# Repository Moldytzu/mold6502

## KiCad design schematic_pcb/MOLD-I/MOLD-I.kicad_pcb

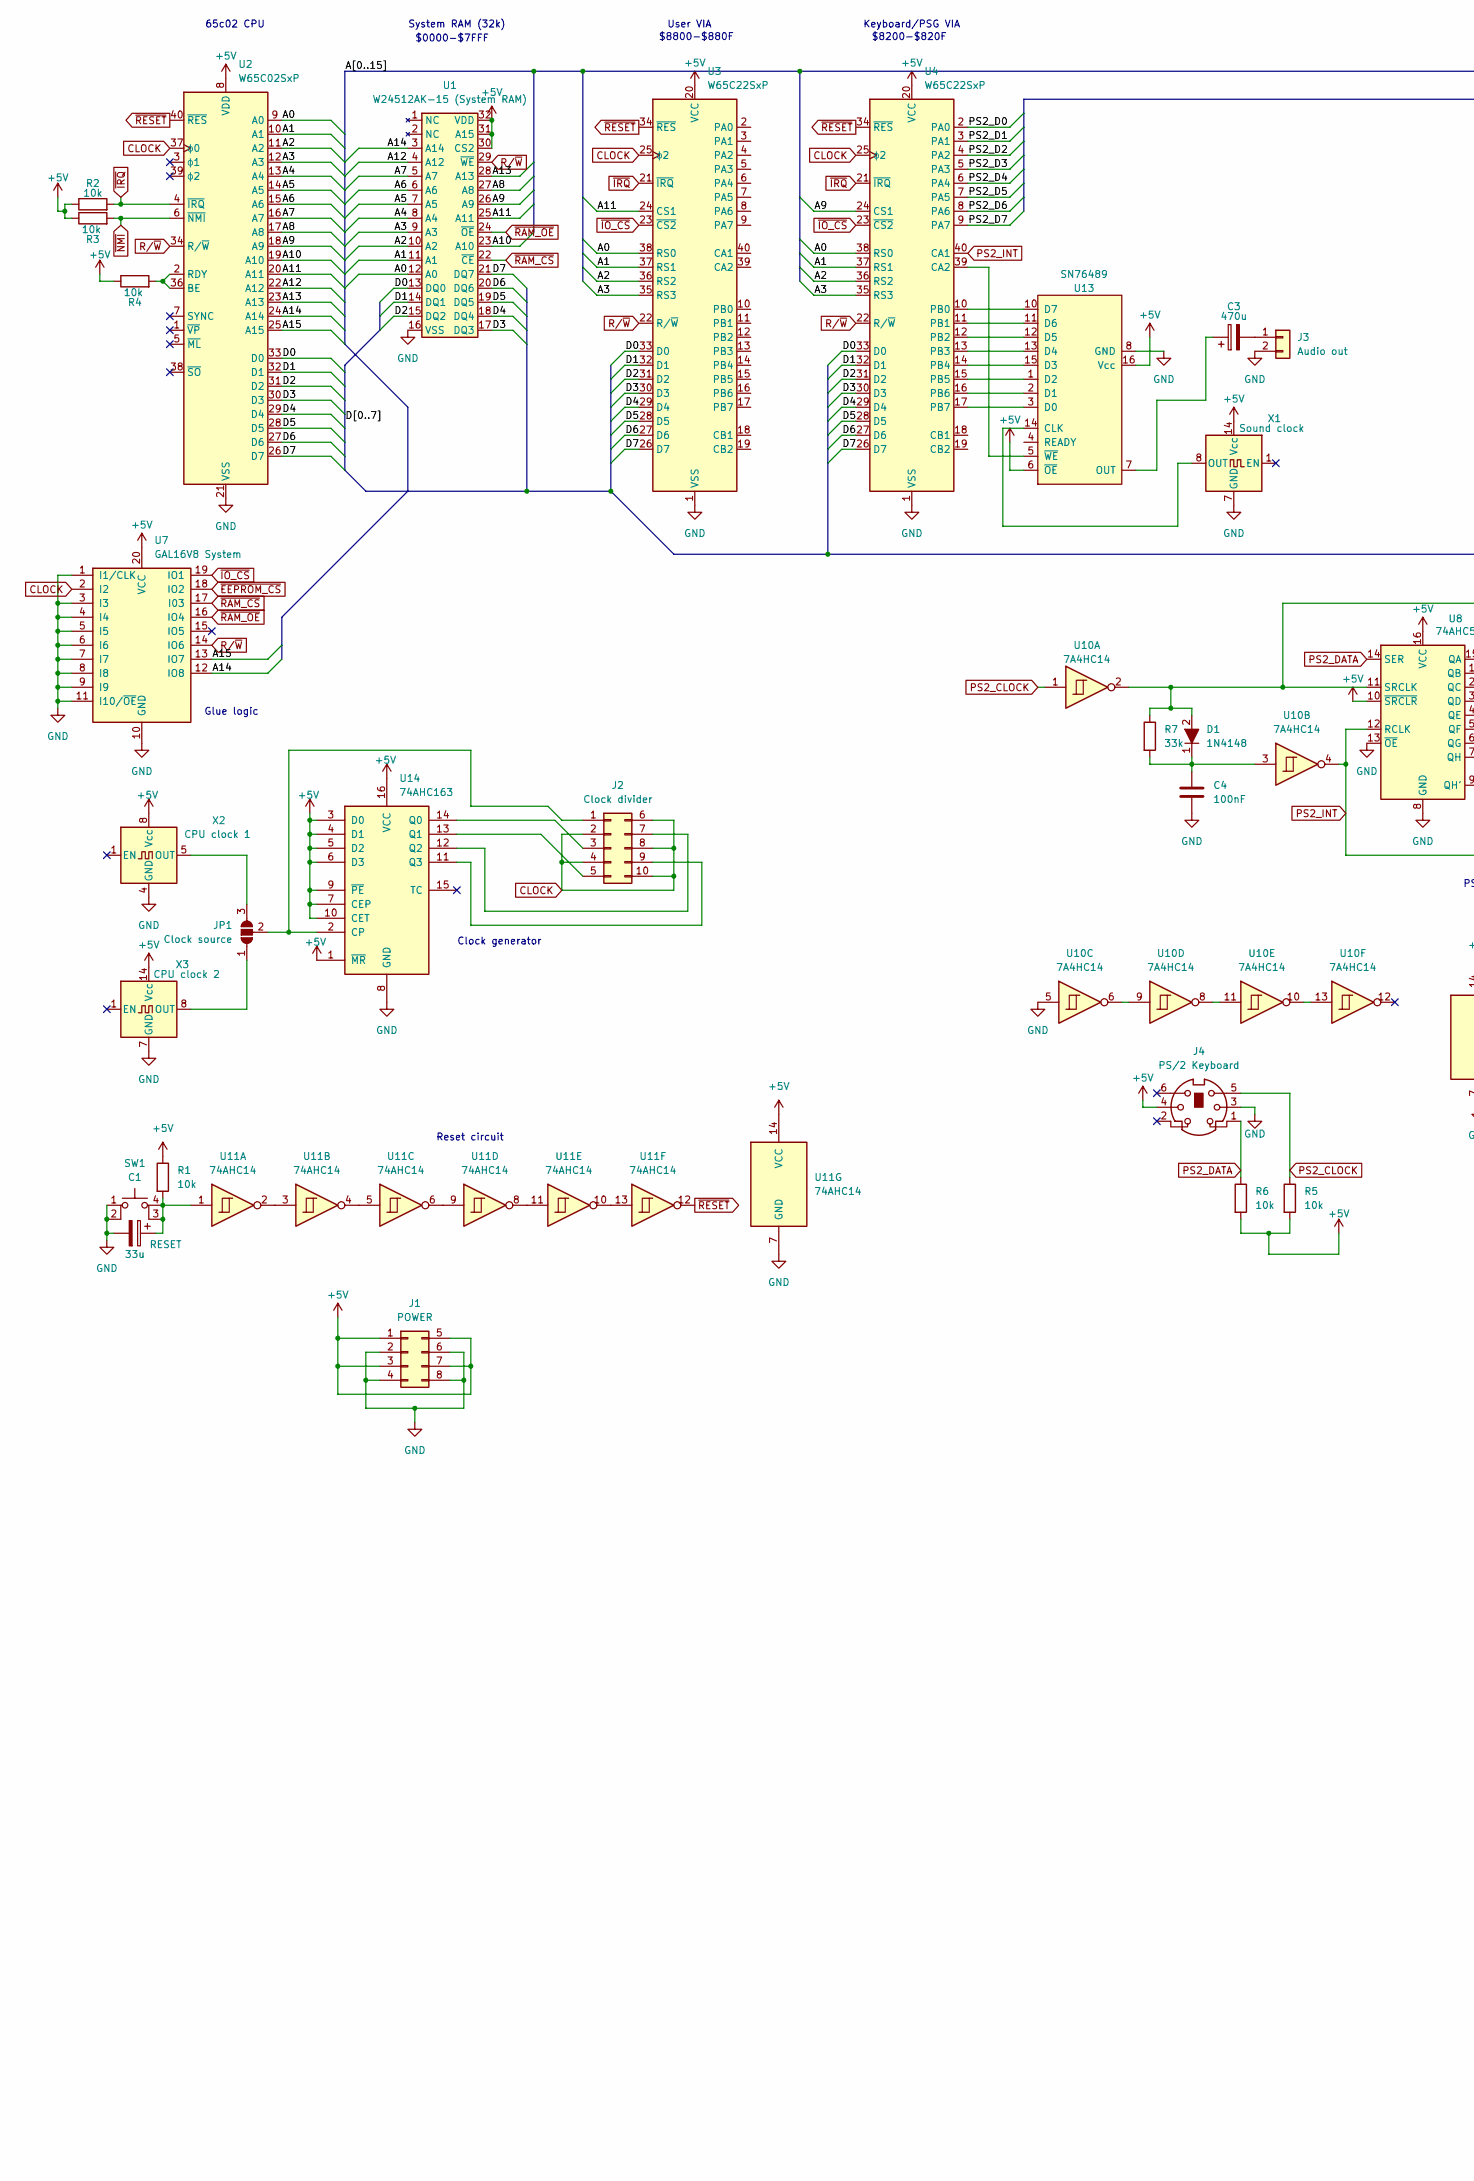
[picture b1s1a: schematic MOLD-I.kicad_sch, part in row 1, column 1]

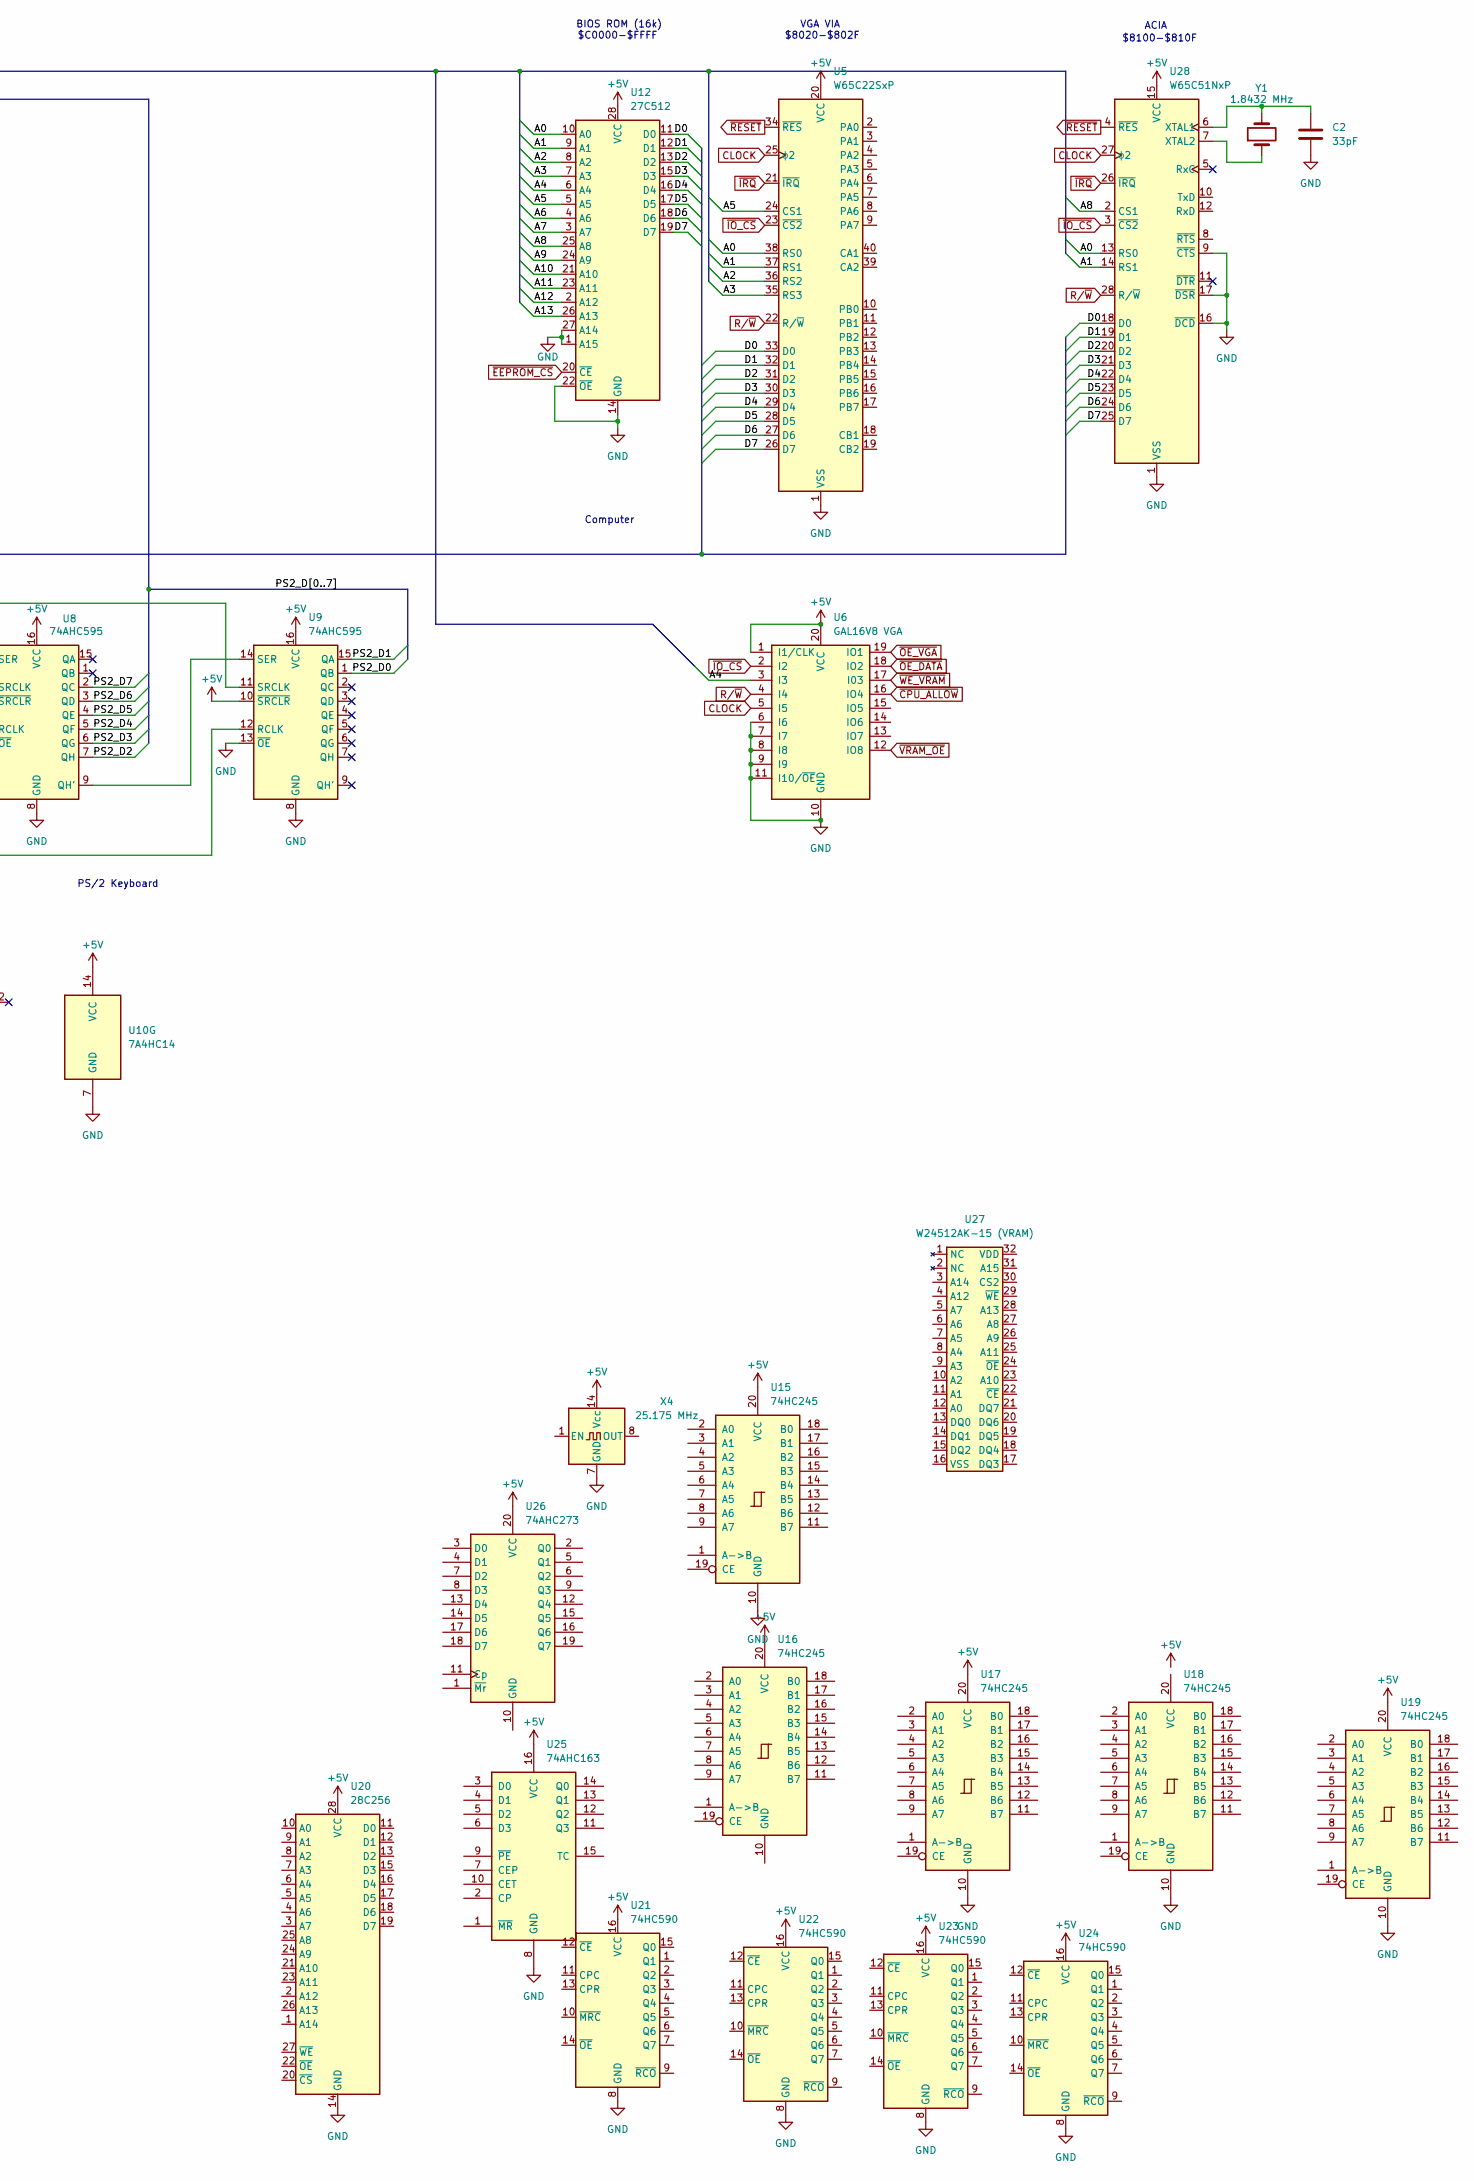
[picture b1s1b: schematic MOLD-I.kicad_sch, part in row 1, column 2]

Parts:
C1: 33u; CP_Radial_D4.0mm_P2.00mm
C2: 33pF; C_Axial_L3.8mm_D2.6mm_P7.50mm_Horizontal
C3: 470u; CP_Radial_D5.0mm_P2.50mm
C4: 100nF; C_Disc_D9.0mm_W2.5mm_P5.00mm
D1: 1N4148; Diode_DO-35_P10mm; MPN 1N4148
J1: POWER; PinHeader_2x04_P2.54mm_Vertical
J2: Clock divider; PinHeader_2x05_P2.54mm_Vertical
J3: Audio out; PinHeader_1x02_P2.54mm_Vertical
J4: PS/2 Keyboard; PinHeader_1x06_P2.54mm_Vertical
JP1: Clock source; PinHeader_1x03_P1.00mm_Vertical
R1, R2, R3, R4, R5, R6: 10k; R_Axial_DIN0204_L3.6mm_D1.6mm_P7.62mm_Horizontal
R7: 33k; R_Axial_DIN0204_L3.6mm_D1.6mm_P7.62mm_Horizontal
SW1: RESET; SW_TH_Tactile_Omron_B3F-10xx
U1: W24512AK-15 (System RAM); DIP-32_W7.62mm
U2: W65C02SxP; DIP-40_W15.24mm
U3, U4, U5: W65C22SxP; DIP-40_W15.24mm
U6: GAL16V8 VGA; DIP-20_W7.62mm
U7: GAL16V8 System; DIP-20_W7.62mm
U8, U9: 74AHC595; DIP-16_W7.62mm
U10: 7A4HC14; DIP-14_W7.62mm
U11: 74AHC14; DIP-14_W7.62mm
U12: 27C512; DIP-28_W15.24mm
U13: SN76489; DIP-16_W7.62mm
U14, U25: 74AHC163; DIP-16_W7.62mm
U15, U16, U17, U18, U19: 74HC245; DIP-20_W7.62mm
U20: 28C256; DIP-28_W15.24mm
U21, U22, U23, U24: 74HC590; DIP-16_W7.62mm
U26: 74AHC273; DIP-20_W7.62mm
U27: W24512AK-15 (VRAM); DIP-32_W7.62mm
U28: W65C51NxP; DIP-28_W15.24mm
X1: Sound clock; Oscillator_DIP-14
X2: CPU clock 1; Oscillator_DIP-8
X3: CPU clock 2; Oscillator_DIP-14
X4: 25.175 MHz; Oscillator_DIP-14
Y1: 1.8432 MHz; Crystal_HC52-U_Vertical

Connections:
+5V: J1.1, J1.3, J1.5, J1.7, J4.4, R1.1, R2.1, R3.1, R4.1, R5.2, R6.2, U1.30 (CS2), U1.31 (A15), U1.32 (VDD), U2.8 (VDD), U3.20 (VCC), U4.20 (VCC), U5.20 (VCC), U6.1 (I1/CLK), U6.20 (VCC), U7.20 (VCC), U8.10 (~SRCLR), U8.16 (VCC), U9.10 (~SRCLR), U9.16 (VCC), U10.14 (VCC), U11.14 (VCC), U12.28 (VCC), U13.6 (~OE), U13.16 (Vcc), U14.1 (~MR), U14.3 (D0), U14.4 (D1), U14.5 (D2), U14.6 (D3), U14.7 (CEP), U14.9 (~PE), U14.10 (CET), U14.16 (VCC), U15.20 (VCC), U16.20 (VCC), U17.20 (VCC), U19.20 (VCC), U20.28 (VCC), U21.16 (VCC), U22.16 (VCC), U23.16 (VCC), U24.16 (VCC), U25.16 (VCC), U26.20 (VCC), U28.15 (VCC), X1.14 (Vcc), X2.8 (Vcc), X3.14 (Vcc), X4.14 (Vcc)
/A0: U1.12 (A0), U2.9 (A0), U3.38 (RS0), U4.38 (RS0), U5.38 (RS0), U12.10 (A0), U28.13 (RS0)
/A1: U1.11 (A1), U2.10 (A1), U3.37 (RS1), U4.37 (RS1), U5.37 (RS1), U12.9 (A1), U28.14 (RS1)
/A2: U1.10 (A2), U2.11 (A2), U3.36 (RS2), U4.36 (RS2), U5.36 (RS2), U12.8 (A2)
/A3: U1.9 (A3), U2.12 (A3), U3.35 (RS3), U4.35 (RS3), U5.35 (RS3), U12.7 (A3)
/A4: U1.8 (A4), U2.13 (A4), U6.3 (I3), U12.6 (A4)
/A5: U1.7 (A5), U2.14 (A5), U5.24 (CS1), U12.5 (A5)
/A6: U1.6 (A6), U2.15 (A6), U12.4 (A6)
/A7: U1.5 (A7), U2.16 (A7), U12.3 (A7)
/A8: U1.27 (A8), U2.17 (A8), U12.25 (A8), U28.2 (CS1)
/A9: U1.26 (A9), U2.18 (A9), U4.24 (CS1), U12.24 (A9)
/A10: U1.23 (A10), U2.19 (A10), U12.21 (A10)
/A11: U1.25 (A11), U2.20 (A11), U3.24 (CS1), U12.23 (A11)
/A12: U1.4 (A12), U2.22 (A12), U12.2 (A12)
/A13: U1.28 (A13), U2.23 (A13), U12.26 (A13)
/A14: U1.3 (A14), U2.24 (A14), U7.12 (IO8)
/A15: U2.25 (A15), U7.13 (IO7)
/D0: U1.13 (DQ0), U2.33 (D0), U3.33 (D0), U4.33 (D0), U5.33 (D0), U12.11 (D0), U28.18 (D0)
/D1: U1.14 (DQ1), U2.32 (D1), U3.32 (D1), U4.32 (D1), U5.32 (D1), U12.12 (D1), U28.19 (D1)
/D2: U1.15 (DQ2), U2.31 (D2), U3.31 (D2), U4.31 (D2), U5.31 (D2), U12.13 (D2), U28.20 (D2)
/D3: U1.17 (DQ3), U2.30 (D3), U3.30 (D3), U4.30 (D3), U5.30 (D3), U12.15 (D3), U28.21 (D3)
/D4: U1.18 (DQ4), U2.29 (D4), U3.29 (D4), U4.29 (D4), U5.29 (D4), U12.16 (D4), U28.22 (D4)
/D5: U1.19 (DQ5), U2.28 (D5), U3.28 (D5), U4.28 (D5), U5.28 (D5), U12.17 (D5), U28.23 (D5)
/D6: U1.20 (DQ6), U2.27 (D6), U3.27 (D6), U4.27 (D6), U5.27 (D6), U12.18 (D6), U28.24 (D6)
/D7: U1.21 (DQ7), U2.26 (D7), U3.26 (D7), U4.26 (D7), U5.26 (D7), U12.19 (D7), U28.25 (D7)
/PS2_D0: U4.2 (PA0), U9.1 (QB)
/PS2_D1: U4.3 (PA1), U9.15 (QA)
/PS2_D2: U4.4 (PA2), U8.7 (QH)
/PS2_D3: U4.5 (PA3), U8.6 (QG)
/PS2_D4: U4.6 (PA4), U8.5 (QF)
/PS2_D5: U4.7 (PA5), U8.4 (QE)
/PS2_D6: U4.8 (PA6), U8.3 (QD)
/PS2_D7: U4.9 (PA7), U8.2 (QC)
CLOCK: J2.2, J2.4, J2.6, J2.8, J2.10, U2.37 (ϕ0), U3.25 (ϕ2), U4.25 (ϕ2), U5.25 (ϕ2), U6.5 (I5), U7.2 (I2), U28.27 (ϕ2)
GND: C1.2, C2.2, C4.2, J1.2, J1.4, J1.6, J1.8, J3.2, J4.3, SW1.1, SW1.2, U1.16 (VSS), U2.21 (VSS), U3.1 (VSS), U4.1 (VSS), U5.1 (VSS), U6.6 (I6), U6.7 (I7), U6.8 (I8), U6.9 (I9), U6.10 (GND), U6.11 (I10/~OE), U7.1 (I1/CLK), U7.3 (I3), U7.4 (I4), U7.5 (I5), U7.6 (I6), U7.7 (I7), U7.8 (I8), U7.9 (I9), U7.10 (GND), U7.11 (I10/~OE), U8.8 (GND), U8.13 (~OE), U9.8 (GND), U9.13 (~OE), U10.5, U10.7 (GND), U11.7 (GND), U12.1 (A15), U12.14 (GND), U12.22 (~OE), U12.27 (A14), U13.8 (GND), U14.8 (GND), U15.10 (GND), U17.10 (GND), U18.10 (GND), U19.10 (GND), U20.14 (GND), U21.8 (GND), U22.8 (GND), U23.8 (GND), U24.8 (GND), U25.8 (GND), U28.1 (VSS), U28.8 (~RTS), U28.9 (~CTS), U28.16 (~DCD), U28.17 (~DSR), X1.7 (GND), X2.4 (GND), X3.7 (GND), X4.7 (GND)
unnamed: C4.1, D1.1, R7.2, U10.3
unnamed: J2.1, JP1.2 (C), U14.2 (CP)
unnamed: J2.3, U14.14 (Q0)
unnamed: J2.5, U14.13 (Q1)
unnamed: J2.7, U14.12 (Q2)
unnamed: J2.9, U14.11 (Q3)
unnamed: C3.2, J3.1
unnamed: JP1.1 (A), X3.8 (OUT)
unnamed: JP1.3 (B), X2.5 (OUT)
unnamed: C1.1, R1.2, SW1.3 (K), SW1.4 (A), U11.1
unnamed: R4.2, U2.2 (RDY), U2.36 (BE)
unnamed: U8.9 (QH'), U9.14 (SER)
unnamed: D1.2, R7.1, U8.11 (SRCLK), U9.11 (SRCLK), U10.2
unnamed: U10.6, U10.9
unnamed: U10.10, U10.13
unnamed: U10.8, U10.11
unnamed: U11.2, U11.3
unnamed: U11.4, U11.5
unnamed: U11.6, U11.9
unnamed: U11.10, U11.13
unnamed: U11.8, U11.11
unnamed: U13.14 (CLK), X1.8 (OUT)
unnamed: U4.17 (PB7), U13.3 (D0)
unnamed: U4.16 (PB6), U13.2 (D1)
unnamed: U4.15 (PB5), U13.1 (D2)
unnamed: U4.14 (PB4), U13.15 (D3)
unnamed: U4.13 (PB3), U13.13 (D4)
unnamed: U4.12 (PB2), U13.12 (D5)
unnamed: U4.11 (PB1), U13.11 (D6)
unnamed: U4.10 (PB0), U13.10 (D7)
unnamed: C3.1, U13.7 (OUT)
unnamed: U4.39 (CA2), U13.5 (~WE)
unnamed: C2.1, U28.6 (XTAL1), Y1.2
unnamed: U28.7 (XTAL2), Y1.1
PS2_CLOCK: J4.5, R5.1, U10.1
PS2_DATA: J4.1, R6.1, U8.14 (SER)
PS2_INT: U4.40 (CA1), U8.12 (RCLK), U9.12 (RCLK), U10.4
R/~W: U1.29 (~WE), U2.34 (R/~W), U3.22 (R/~W), U4.22 (R/~W), U5.22 (R/~W), U6.4 (I4), U7.14 (IO6), U28.28 (R/~W)
~CPU_ALLOW: U6.16 (IO4)
~EEPROM_CS: U7.18 (IO2), U12.20 (~CE)
~IO_CS: U3.23 (~CS2), U4.23 (~CS2), U5.23 (~CS2), U6.2 (I2), U7.19 (IO1), U28.3 (~CS2)
~IRQ: R2.2, U2.4 (~IRQ), U3.21 (~IRQ), U4.21 (~IRQ), U5.21 (~IRQ), U28.26 (~IRQ)
~NMI: R3.2, U2.6 (~NMI)
~OE_DATA: U6.18 (IO2)
~OE_VGA: U6.19 (IO1)
~RAM_CS: U1.22 (~CE), U7.17 (I03)
~RAM_OE: U1.24 (~OE), U7.16 (IO4)
~RESET: U2.40 (~RES), U3.34 (~RES), U4.34 (~RES), U5.34 (~RES), U11.12, U28.4 (~RES)
~VRAM_OE: U6.12 (IO8)
~WE_VRAM: U6.17 (I03)

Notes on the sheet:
System RAM (32k)
$C0000-$FFFF
$8020-$802F
Reset circuit
$8200-$820F
ACIA
Glue logic
User VIA
Computer
$0000-$7FFF
65c02 CPU
PS/2 Keyboard
$8100-$810F
Clock generator
VGA VIA
$8800-$880F
BIOS ROM (16k)
Keyboard/PSG VIA

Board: 2 copper layers, 51 parts (0 on the bottom side), 80 nets, no tracks yet.

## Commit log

2024-01-03 basic bios and emulation
2024-01-04 bios: add lcd print macro
2024-01-05 swap assemblers
2024-05-07 add lots of stuff
2024-07-03 ie multe ie multe
